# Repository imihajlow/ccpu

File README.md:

A 74xx discrete logic IC-based computer.

Folder structure:
* `doc` - documentation
* `model` - Verilog model and test benches
* `boards` - KiCAD designs of the computer
* `tools` - various tools: ALU generator, assembler, linker, compiler, simulator.
* `app` - software tests and applications

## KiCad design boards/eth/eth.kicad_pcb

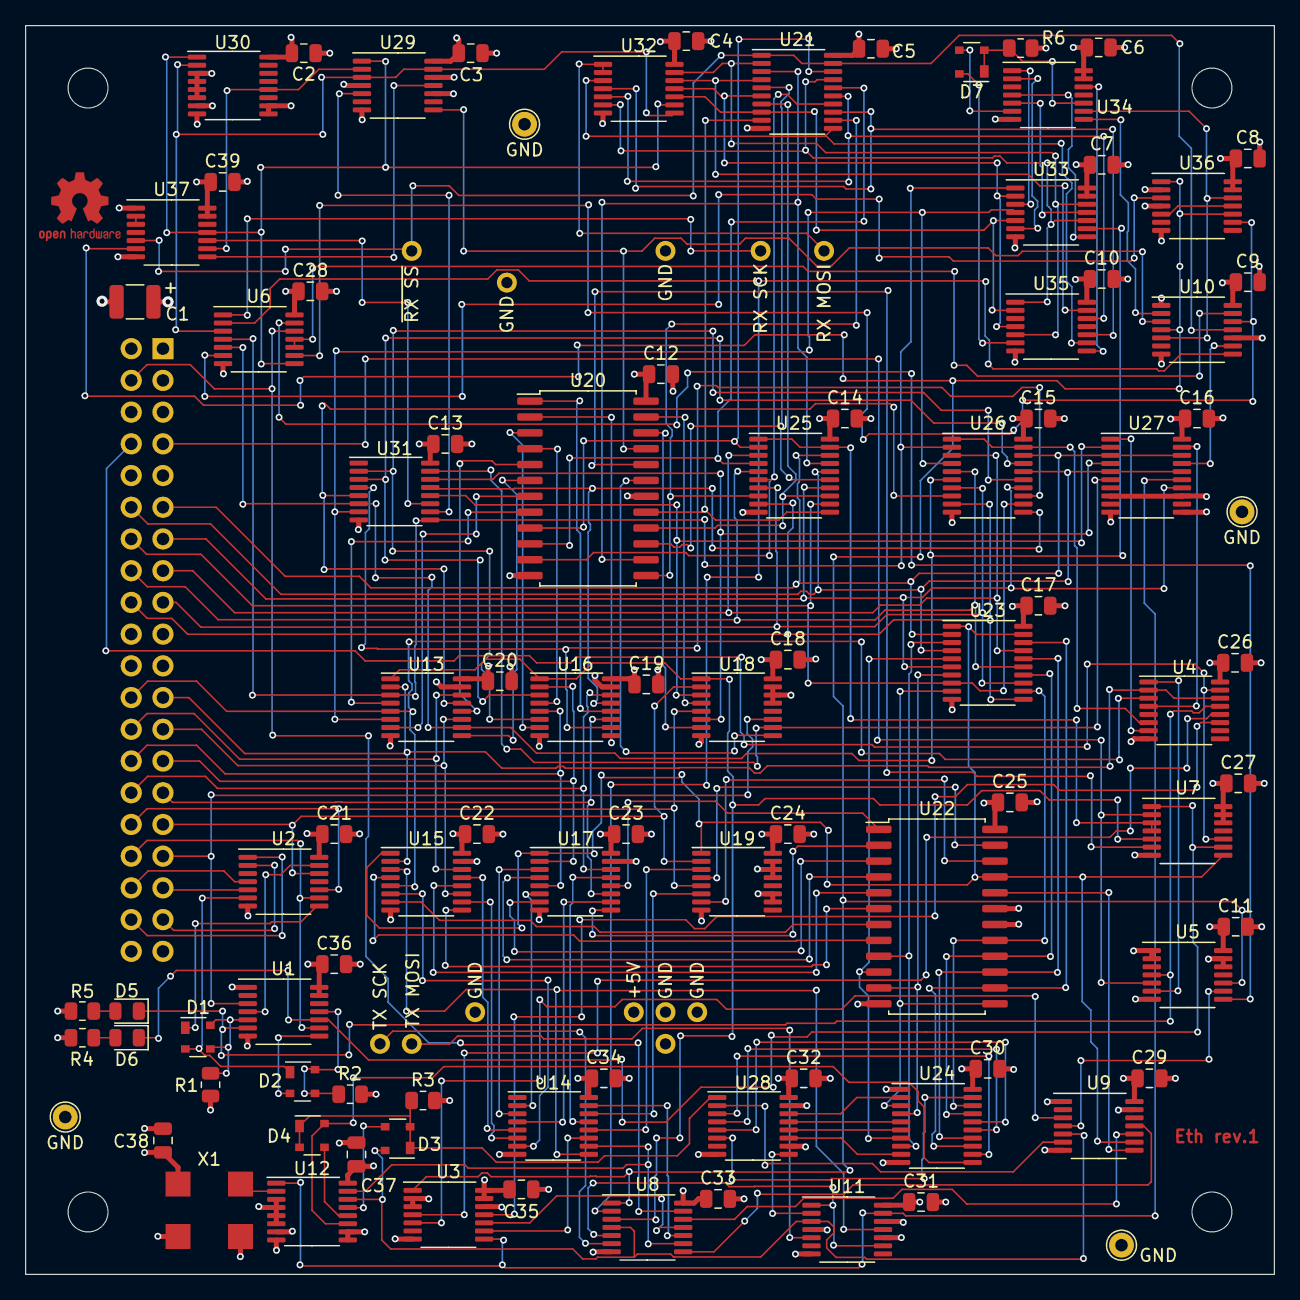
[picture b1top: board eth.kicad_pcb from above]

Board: 4 copper layers, 100.0 x 100.0 mm, 100 parts (1 on the bottom side), 173 nets.

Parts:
C1: 33.0x10v; C_1210_3225Metric
C2, C3, C4, C5, C6, C7, C8, C9, C10, C11, C12, C13, C14, C15, C16, C17, C18, C19, C20, C21, C22, C23, C24, C25, C26, C27, C28, C29, C30, C31, C32, C33, C34, C35, C36, C37, C38, C39: 0.1; C_0805_2012Metric
D1, D2, D3, D4, D7: BAT74; SOT-143
D5, D6: LED; LED_0805_2012Metric
H1, H2, H3, H4: MountingHole; MountingHole_3.2mm_M3
J1: Conn_02x20_Odd_Even; PinHeader_2x20_P2.54mm_Horizontal
J2: eth-phy-shield-conn; partial-nucleo64
R1, R2, R3, R6: 1k; R_0805_2012Metric
R4, R5: 500; R_0805_2012Metric
TP1, TP2, TP3, TP4: GND; TestPoint_THTPad_D2.0mm_Drill1.0mm
U1, U9, U37: 74HC04; TSSOP-14_4.4x5mm_P0.65mm
U2, U34, U35: 74HC21; TSSOP-14_4.4x5mm_P0.65mm
U3, U10, U11, U29, U36: 74HC74; TSSOP-14_4.4x5mm_P0.65mm
U4: 74HC139; TSSOP-16_4.4x5mm_P0.65mm
U5, U7: 74HC32; TSSOP-14_4.4x5mm_P0.65mm
U6, U8: 74HC08; TSSOP-14_4.4x5mm_P0.65mm
U12, U30: 74HC161; TSSOP-16_4.4x5mm_P0.65mm
U13, U15, U16, U17, U18, U19: 74HC157; TSSOP-16_4.4x5mm_P0.65mm
U14, U31: 74HC4040; TSSOP-16_4.4x5mm_P0.65mm
U20, U22: 6116; SOIC-24W_7.5x15.4mm_P1.27mm
U21, U23, U25, U26, U27: 74HC244; TSSOP-20_4.4x6.5mm_P0.65mm
U24: 74HC273; TSSOP-20_4.4x6.5mm_P0.65mm
U28: 74HC165; TSSOP-16_4.4x5mm_P0.65mm
U32: 74HC164; TSSOP-14_4.4x5mm_P0.65mm
U33: 74HC86; TSSOP-14_4.4x5mm_P0.65mm
X1: CB3-3C-20M; Oscillator_SMD_EuroQuartz_XO91-4Pin_7.0x5.0mm

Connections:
/a0: J1.23, U4.2 (A0), U4.14 (A0), U13.2 (I0a), U15.2 (I0a)
/a1: J1.24, U4.3 (A1), U13.5 (I0b), U15.5 (I0b)
/a2: J1.25, U13.11 (I0c), U15.11 (I0c)
/a3: J1.26, U13.14 (I0d), U15.14 (I0d)
/a4: J1.27, U16.2 (I0a), U17.2 (I0a)
/a5: J1.28, U16.5 (I0b), U17.5 (I0b)
/a6: J1.29, U16.11 (I0c), U17.11 (I0c)
/a7: J1.30, U16.14 (I0d), U17.14 (I0d)
/a8: J1.31, U2.12, U18.2 (I0a), U19.2 (I0a)
/a9: J1.32, U2.10, U18.5 (I0b), U19.5 (I0b)
/a10: J1.33, U1.3, U18.11 (I0c)
/a11: J1.34, U1.9, U2.9
/a12: J1.35, U2.5
/a13: J1.36, U2.4
/a14: J1.37, U2.2
/a15: J1.38, U2.1
/a_89nab_set: D1.1 (C1), U2.8
/a_cdef_set: D1.2 (C2), D2.1 (C1), U2.6
/buf_full: U10.9 (Q), U27.17 (2A0)
/d0: J1.11, U23.2 (1A0), U25.18 (1Y0), U26.18 (1Y0), U27.3 (2Y0), U27.18 (1Y0)
/d1: J1.12, U23.4 (1A1), U25.16 (1Y1), U26.16 (1Y1), U27.5 (2Y1), U27.16 (1Y1)
/d2: J1.13, U23.6 (1A2), U25.14 (1Y2), U26.14 (1Y2), U27.14 (1Y2)
/d3: J1.14, U23.8 (1A3), U25.12 (1Y3), U26.12 (1Y3)
/d4: J1.15, U23.17 (2A0), U25.3 (2Y0), U26.3 (2Y0)
/d5: J1.16, U23.15 (2A1), U25.5 (2Y1), U26.5 (2Y1)
/d6: J1.17, U23.13 (2A2), U25.7 (2Y2), U26.7 (2Y2)
/d7: J1.18, U23.11 (2A3), U25.9 (2Y3), U26.9 (2Y3)
/filter/a02: U6.6, U36.3 (C)
/filter/d_4320_mac: D7.3 (A2), U34.6
/filter/d_4320_ok: D7.1 (C1), D7.2 (C2), R6.2, U34.10
/filter/d_4320_set: D7.4 (A1), U35.6
/filter/d_7651_set: U34.12, U35.8
/filter/d_xor_a0: U33.3, U34.1
/filter/d_xor_a1: U33.6, U34.2
/filter/d_xor_a2: U33.8, U34.4
/filter/last_mac_ok: U10.5 (Q), U34.9, U36.12 (D)
/filter/mac_end: U36.5 (Q), U36.11 (C)
/filter/next_mac_ok: U10.2 (D), U34.8
/filter/~d0: U33.11, U34.5
/rearm_sched: U3.5 (Q), U9.3
/receiver/bit_count2: U29.2 (D), U30.12 (Q2), U37.9
/receiver/byte_clk: U29.5 (Q), U31.10 (CP)
/receiver/rst: U31.11 (MR), U37.10
/receiver/sck_f: U6.3, U29.3 (C), U29.13 (~R), U30.2 (CP), U32.8 (CP)
/receiver/~bit_count_2: U29.11 (C), U37.8
/recv_a0: U13.4 (Za), U20.8 (A0)
/recv_a1: U13.7 (Zb), U20.7 (A1)
/recv_a2: U13.9 (Zc), U20.6 (A2)
/recv_a3: U13.12 (Zd), U20.5 (A3)
/recv_a4: U16.4 (Za), U20.4 (A4)
/recv_a5: U16.7 (Zb), U20.3 (A5)
/recv_a6: U16.9 (Zc), U20.2 (A6)
/recv_a7: U16.12 (Zd), U20.1 (A7)
/recv_a8: U18.4 (Za), U20.23 (A8)
/recv_a9: U18.7 (Zb), U20.22 (A9)
/recv_a10: U18.9 (Zc), U20.19 (A10)
/recv_a_sel: U7.5, U8.3, U13.1 (S), U16.1 (S), U18.1 (S)
/recv_byte0: U21.2 (1A0), U32.13 (Q7), U33.12, U35.5
/recv_byte1: U21.4 (1A1), U32.12 (Q6), U35.13
/recv_byte2: U21.6 (1A2), U32.11 (Q5), U33.2, U35.4
/recv_byte3: U21.8 (1A3), U32.10 (Q4), U33.5, U35.2
/recv_byte4: U21.17 (2A0), U32.6 (Q3), U33.10, U35.1
/recv_byte5: U21.15 (2A1), U32.5 (Q2), U35.12
/recv_byte6: U21.13 (2A2), U32.4 (Q1), U35.10
/recv_byte7: U21.11 (2A3), U32.3 (Q0), U35.9
/recv_byte_cnt0: U6.4, U13.3 (I1a), U26.2 (1A0), U31.9 (Q0), U33.1
/recv_byte_cnt1: U13.6 (I1b), U26.4 (1A1), U31.7 (Q1), U33.4
/recv_byte_cnt2: U6.5, U13.10 (I1c), U26.6 (1A2), U31.6 (Q2), U33.9
/recv_byte_cnt3: U13.13 (I1d), U26.8 (1A3), U31.5 (Q3)
/recv_byte_cnt4: U16.3 (I1a), U26.17 (2A0), U31.3 (Q4)
/recv_byte_cnt5: U16.6 (I1b), U26.15 (2A1), U31.2 (Q5)
/recv_byte_cnt6: U16.10 (I1c), U26.13 (2A2), U31.4 (Q6)
/recv_byte_cnt7: U16.13 (I1d), U26.11 (2A3), U31.13 (Q7)
/recv_byte_cnt8: U18.3 (I1a), U27.2 (1A0), U31.12 (Q8)
/recv_byte_cnt9: U18.6 (I1b), U27.4 (1A1), U31.14 (Q9)
/recv_byte_cnt10: U18.10 (I1c), U27.6 (1A2), U31.15 (Q10)
/recv_d0: U20.9 (D0), U21.18 (1Y0), U25.2 (1A0)
/recv_d1: U20.10 (D1), U21.16 (1Y1), U25.4 (1A1)
/recv_d2: U20.11 (D2), U21.14 (1Y2), U25.6 (1A2)
/recv_d3: U20.13 (D3), U21.12 (1Y3), U25.8 (1A3)
/recv_d4: U20.14 (D4), U21.3 (2Y0), U25.17 (2A0)
/recv_d5: U20.15 (D5), U21.5 (2Y1), U25.15 (2A1)
/recv_d6: U20.16 (D6), U21.7 (2Y2), U25.13 (2A2)
/recv_d7: U20.17 (D7), U21.9 (2Y3), U25.11 (2A3)
/recv_mosi: J2.PB13, U32.1 (DSA), U32.2 (DSB)
/recv_sck: J2.PB15, U6.1
/recv_sck_ena: U6.2, U8.2, U10.8 (~Q)
/recv_ss: U3.1 (~R), U5.10, U8.1, U10.4 (~S), U36.1 (~R), U36.10 (~S), U37.6
/tx_a0: U15.4 (Za), U22.8 (A0)
/tx_a1: U15.7 (Zb), U22.7 (A1)
/tx_a2: U15.9 (Zc), U22.6 (A2)
/tx_a3: U15.12 (Zd), U22.5 (A3)
/tx_a4: U17.4 (Za), U22.4 (A4)
/tx_a5: U17.7 (Zb), U22.3 (A5)
/tx_a6: U17.9 (Zc), U22.2 (A6)
/tx_a7: U17.12 (Zd), U22.1 (A7)
/tx_a8: U19.4 (Za), U22.23 (A8)
/tx_a9: U19.7 (Zb), U22.22 (A9)
/tx_buf_d0: U24.9 (Q3), U28.11 (D0)
/tx_buf_d1: U24.6 (Q2), U28.12 (D1)
/tx_buf_d2: U24.5 (Q1), U28.13 (D2)
/tx_buf_d3: U24.2 (Q0), U28.14 (D3)
/tx_buf_d4: U24.12 (Q4), U28.3 (D4)
/tx_buf_d5: U24.15 (Q5), U28.4 (D5)
/tx_buf_d6: U24.16 (Q6), U28.5 (D6)
/tx_buf_d7: U24.19 (Q7), U28.6 (D7)
/tx_byte_cnt0: U11.11 (C), U14.9 (Q0), U15.3 (I1a)
/tx_byte_cnt1: U14.7 (Q1), U15.6 (I1b)
/tx_byte_cnt2: U14.6 (Q2), U15.10 (I1c)
/tx_byte_cnt3: U14.5 (Q3), U15.13 (I1d)
/tx_byte_cnt4: U14.3 (Q4), U17.3 (I1a)
/tx_byte_cnt5: U14.2 (Q5), U17.6 (I1b)
/tx_byte_cnt6: U14.4 (Q6), U17.10 (I1c)
/tx_byte_cnt7: U14.13 (Q7), U17.13 (I1d)
/tx_byte_cnt8: U14.12 (Q8), U19.3 (I1a)
/tx_byte_cnt9: U14.14 (Q9), U19.6 (I1b)
/tx_byte_cnt10: U8.10, U14.15 (Q10)
/tx_cnt0: D3.4 (A1), U8.4, U9.5, U11.3 (C), U12.14 (Q0)
/tx_cnt1: D3.3 (A2), U12.13 (Q1)
/tx_cnt2: D4.3 (A2), U12.12 (Q2)
/tx_cnt3: D4.4 (A1), U12.11 (Q3), U24.11 (Cp)
/tx_cp_in: U12.2 (CP), X1.3 (OUT)
/tx_d0: U22.14 (D4), U23.18 (1Y0), U24.13 (D4)
/tx_d1: U22.15 (D5), U23.16 (1Y1), U24.14 (D5)
/tx_d2: U22.16 (D6), U23.14 (1Y2), U24.17 (D6)
/tx_d3: U22.17 (D7), U23.12 (1Y3), U24.18 (D7)
/tx_d4: U22.9 (D0), U23.3 (2Y0), U24.8 (D3)
/tx_d5: U22.10 (D1), U23.5 (2Y1), U24.7 (D2)
/tx_d6: U22.11 (D2), U23.7 (2Y2), U24.4 (D1)
/tx_d7: U22.13 (D3), U23.9 (2Y3), U24.3 (D0)
/tx_finish: U8.8, U9.11
/tx_halt: U3.9 (Q), U14.11 (MR)
/tx_mosi: J2.PC12, U11.5 (Q)
/tx_oe: U8.5, U11.1 (~R), U11.9 (Q)
/tx_sck: J2.PC10, U8.6
/tx_shift_cp: U9.6, U28.2 (CP)
/tx_shift_q7: U11.2 (D), U28.9 (Q7)
/~a10: U1.4, U2.13
/~a11: D2.2 (C2), U1.8
/~a_buf_sel: D6.1 (K), U1.10, U7.1, U7.9
/~a_fbxx: D5.1 (K), U1.6, U4.13 (A1), U5.4
/~clr_frame_received: U6.10, U6.11, U10.13 (~R)
/~inhibit: U6.9, U10.12 (D), U36.9 (Q)
/~oe_cr_to_d: U4.4 (O0), U27.19 (2OE)
/~oe: J1.7, U5.5, U7.2
/~rearm_req: U3.4 (~S), U4.12 (O0)
/~rearm_sched: U5.9, U9.4
/~rearm: U5.8, U6.13
/~recv_buf_oe: U7.6, U20.20 (~OE)
/~recv_buf_we: U10.3 (C), U20.21 (~WE), U29.8 (~Q)
/~recv_byte_cnt_hi_oe: U4.7 (O3), U27.1 (1OE)
/~recv_byte_cnt_lo_oe: U4.6 (O2), U26.1 (1OE), U26.19 (2OE)
/~recv_d_oe: U7.3, U7.4, U25.1 (1OE), U25.19 (2OE)
/~recv_rst: U6.8, U29.1 (~R), U30.1 (~MR), U32.9 (~MR), U37.11
/~recv_ss: J2.PC6, U10.11 (C), U21.1 (1OE), U21.19 (2OE), U37.5
/~reg_oe_ena: U4.1 (E), U5.6
/~rst: J1.4, U6.12, U8.13
/~tx_buf_oe: U9.8, U22.20 (~OE)
/~tx_buf_we: U7.8, U9.9, U15.1 (S), U17.1 (S), U19.1 (S), U22.21 (~WE), U23.1 (1OE), U23.19 (2OE)
/~tx_byte_clk: U8.9, U12.15 (TC), U14.10 (CP)
/~tx_finish: U8.12, U9.10
/~tx_halt_set: U3.10 (~S), U8.11
/~tx_halt: U3.8 (~Q), U11.13 (~R), U12.1 (~MR), U27.15 (2A1)
/~tx_req: U3.11 (C), U4.11 (O1)
/~tx_shift_pl: D3.1 (C1), D3.2 (C2), D4.1 (C1), D4.2 (C2), R3.1, U28.1 (~PL)
/~we: J1.8, U4.15 (E), U7.10
GND: C1.2, C2.2, C3.2, C4.2, C5.2, C6.2, C7.2, C8.2, C9.2, C10.2, C11.2, C12.2, C13.2, C14.2, C15.2, C16.2, C17.2, C18.2, C19.2, C20.2, C21.2, C22.2, C23.2, C24.2, C25.2, C26.2, C27.2, C28.2, C29.2, C30.2, C31.2, C32.2, C33.2, C34.2, C35.2, C36.2, C37.2, C38.2, C39.2, J1.2, J1.39, J2.GND, R3.2, R6.1, TP1.1, TP2.1, TP3.1, TP4.1, U1.1, U1.7 (GND), U2.7 (GND), U3.2 (D), U3.3 (C), U3.7 (GND), U3.12 (D), U4.8 (GND), U5.1, U5.2, U5.7 (GND), U5.12, U5.13, U6.7 (GND), U7.7 (GND), U8.7 (GND), U9.1, U9.7 (GND), U9.13, U10.7 (GND), U11.7 (GND), U12.3 (D0), U12.4 (D1), U12.5 (D2), U12.6 (D3), U12.8 (GND), U13.8 (GND), U13.15 (E), U14.8 (GND), U15.8 (GND), U15.15 (E), U16.8 (GND), U16.15 (E), U17.8 (GND), U17.15 (E), U18.8 (GND), U18.13 (I1d), U18.14 (I0d), U18.15 (E), U19.8 (GND), U19.10 (I1c), U19.11 (I0c), U19.13 (I1d), U19.14 (I0d), U19.15 (E), U20.12 (GND), U20.18 (~CS), U21.10 (GND), U22.12 (GND), U22.18 (~CS), U22.19 (A10), U23.10 (GND), U24.10 (GND), U25.10 (GND), U26.10 (GND), U27.8 (1A3), U27.10 (GND), U27.11 (2A3), U27.13 (2A2), U28.8 (GND), U28.10 (DS), U28.15 (~CE), U29.7 (GND), U30.3 (D0), U30.4 (D1), U30.5 (D2), U30.6 (D3), U30.8 (GND), U31.8 (GND), U32.7 (GND), U33.7 (GND), U34.7 (GND), U35.7 (GND), U36.7 (GND), U37.1, U37.7 (GND), X1.2 (GND)
unnamed: D1.3 (A2), D1.4 (A1), R1.2, U1.5
unnamed: D2.3 (A2), D2.4 (A1), R2.1, U1.11
unnamed: D5.2 (A), R5.1
unnamed: D6.2 (A), R4.2
unnamed: U37.2, U37.3
VCC: C1.1, C2.1, C3.1, C4.1, C5.1, C6.1, C7.1, C8.1, C9.1, C10.1, C11.1, C12.1, C13.1, C14.1, C15.1, C16.1, C17.1, C18.1, C19.1, C20.1, C21.1, C22.1, C23.1, C24.1, C25.1, C26.1, C27.1, C28.1, C29.1, C30.1, C31.1, C32.1, C33.1, C34.1, C35.1, C36.1, C37.1, C38.1, C39.1, J1.1, J1.40, J2.+5V, R1.1, R2.2, R4.1, R5.2, U1.13, U1.14 (VCC), U2.14 (VCC), U3.13 (~R), U3.14 (VCC), U4.16 (VCC), U5.14 (VCC), U6.14 (VCC), U7.12, U7.13, U7.14 (VCC), U8.14 (VCC), U9.14 (VCC), U10.1 (~R), U10.10 (~S), U10.14 (VCC), U11.4 (~S), U11.10 (~S), U11.12 (D), U11.14 (VCC), U12.7 (CEP), U12.9 (~PE), U12.10 (CET), U12.16 (VCC), U13.16 (VCC), U14.16 (VCC), U15.16 (VCC), U16.16 (VCC), U17.16 (VCC), U18.16 (VCC), U19.16 (VCC), U20.24 (VCC), U21.20 (VCC), U22.24 (VCC), U23.20 (VCC), U24.1 (~Mr), U24.20 (VCC), U25.20 (VCC), U26.20 (VCC), U27.20 (VCC), U28.16 (VCC), U29.4 (~S), U29.10 (~S), U29.12 (D), U29.14 (VCC), U30.7 (CEP), U30.9 (~PE), U30.10 (CET), U30.16 (VCC), U31.16 (VCC), U32.14 (VCC), U33.13, U33.14 (VCC), U34.13, U34.14 (VCC), U35.14 (VCC), U36.2 (D), U36.4 (~S), U36.13 (~R), U36.14 (VCC), U37.13, U37.14 (VCC), X1.1 (EN), X1.4 (V+)

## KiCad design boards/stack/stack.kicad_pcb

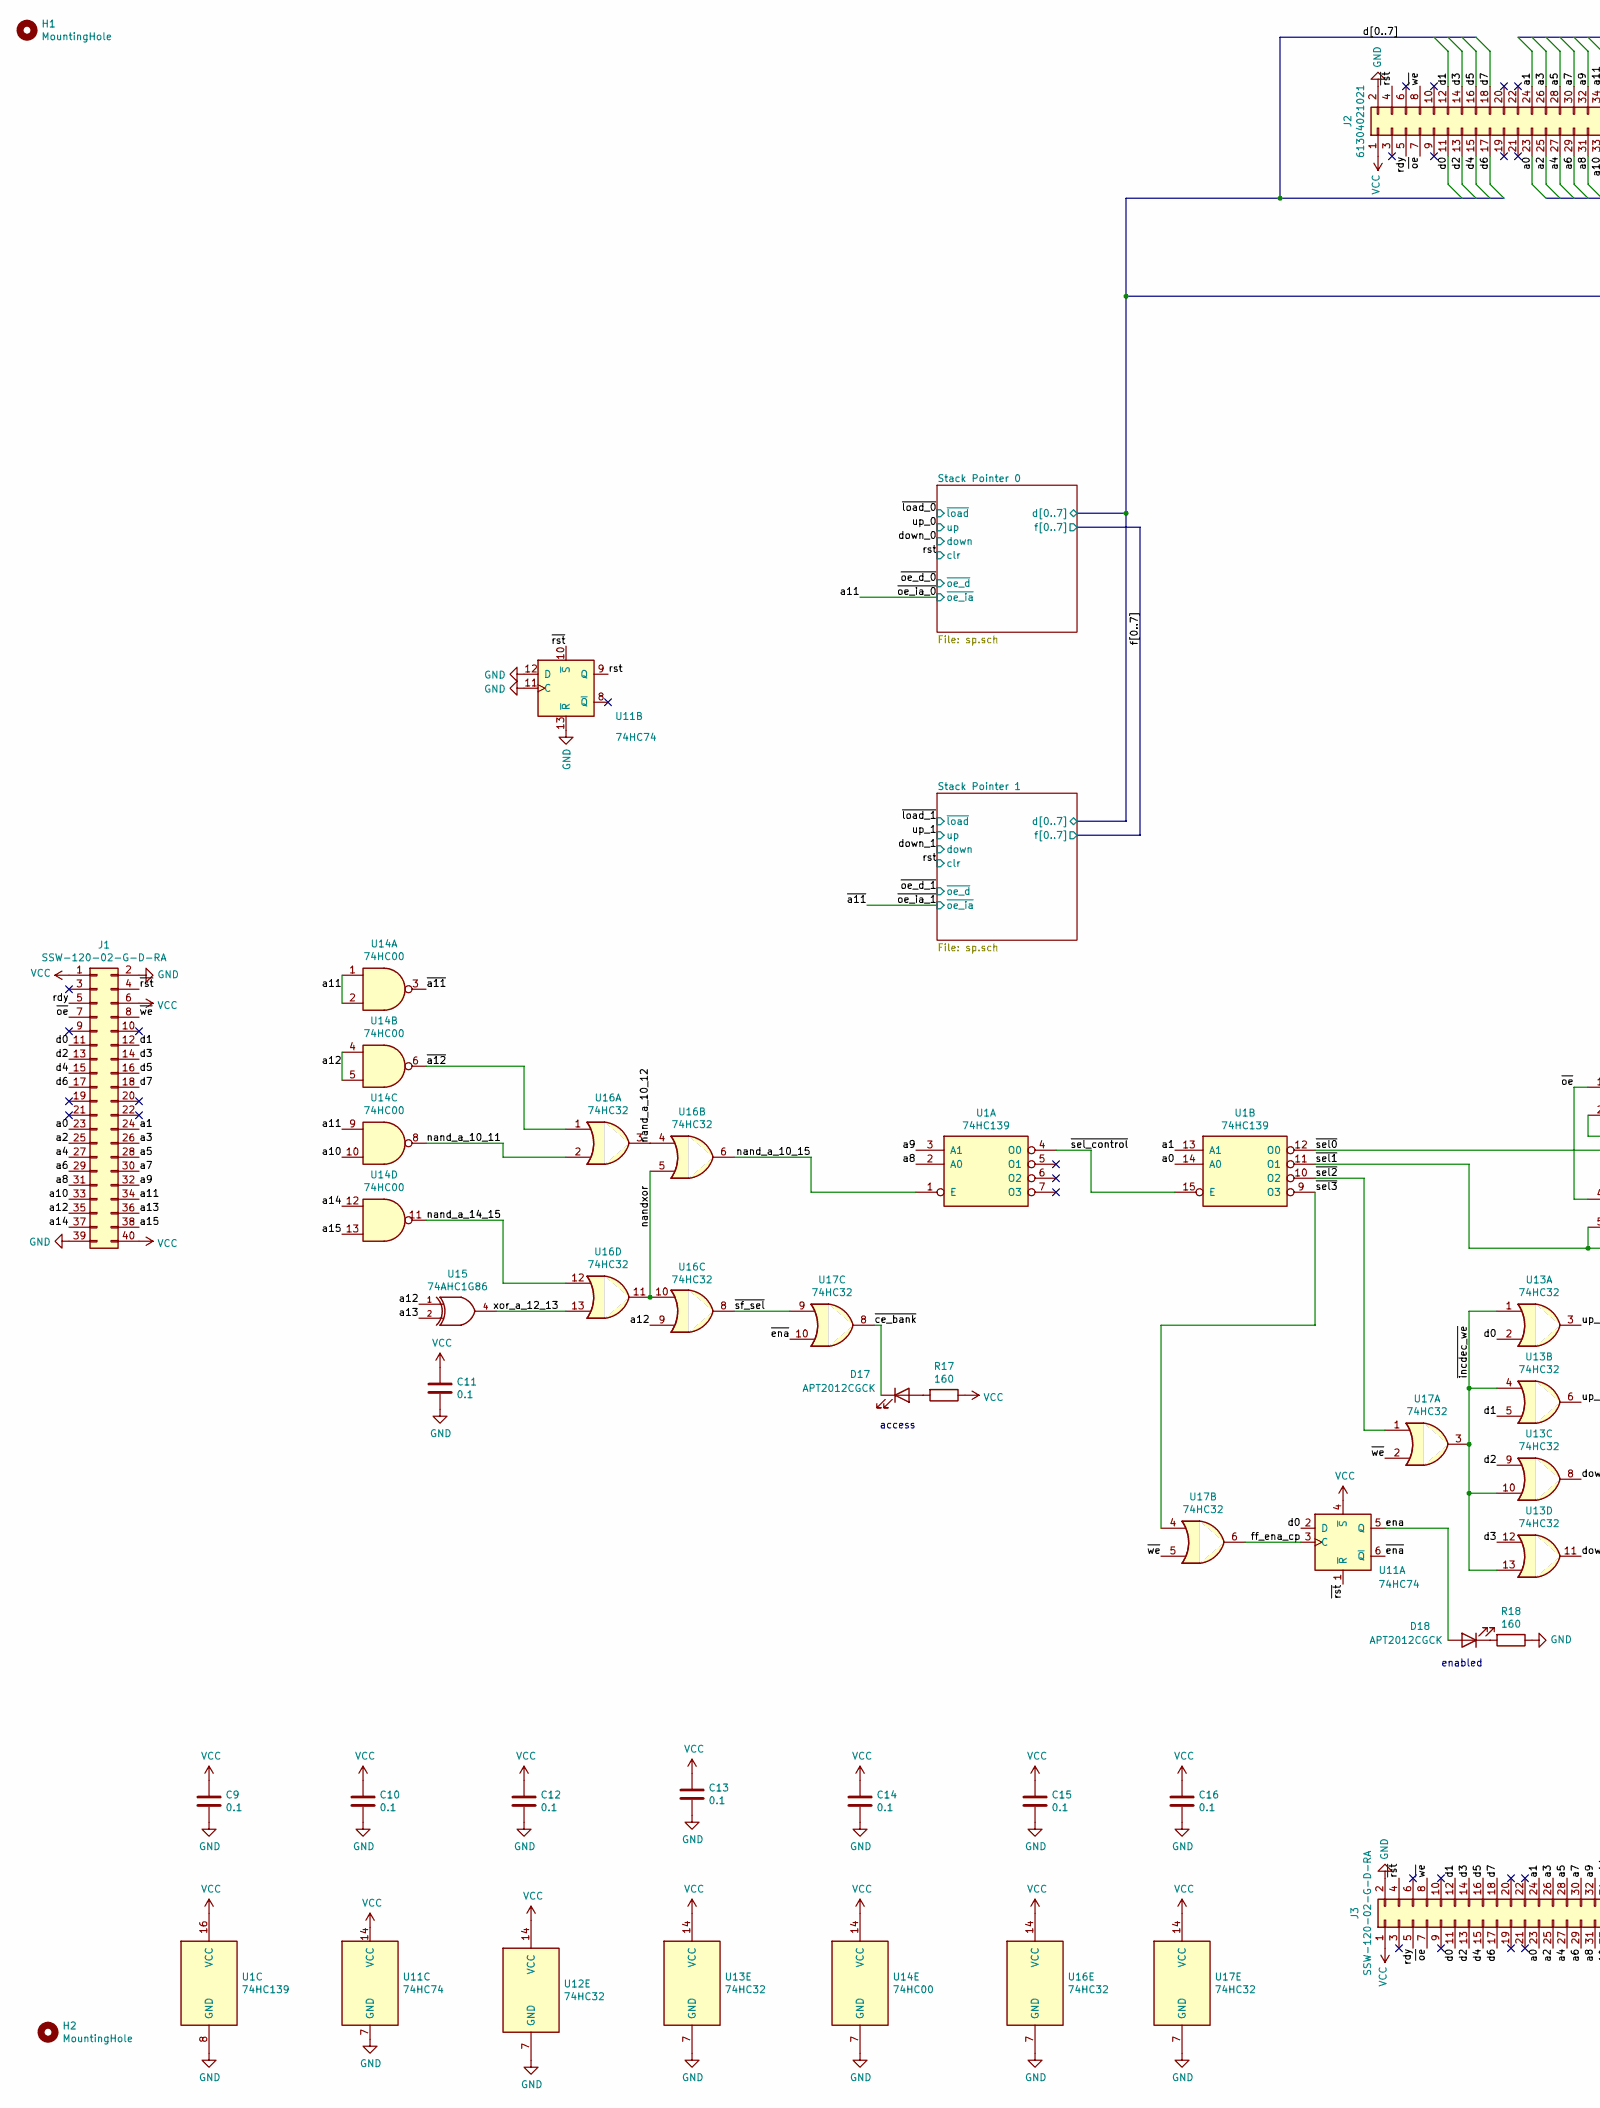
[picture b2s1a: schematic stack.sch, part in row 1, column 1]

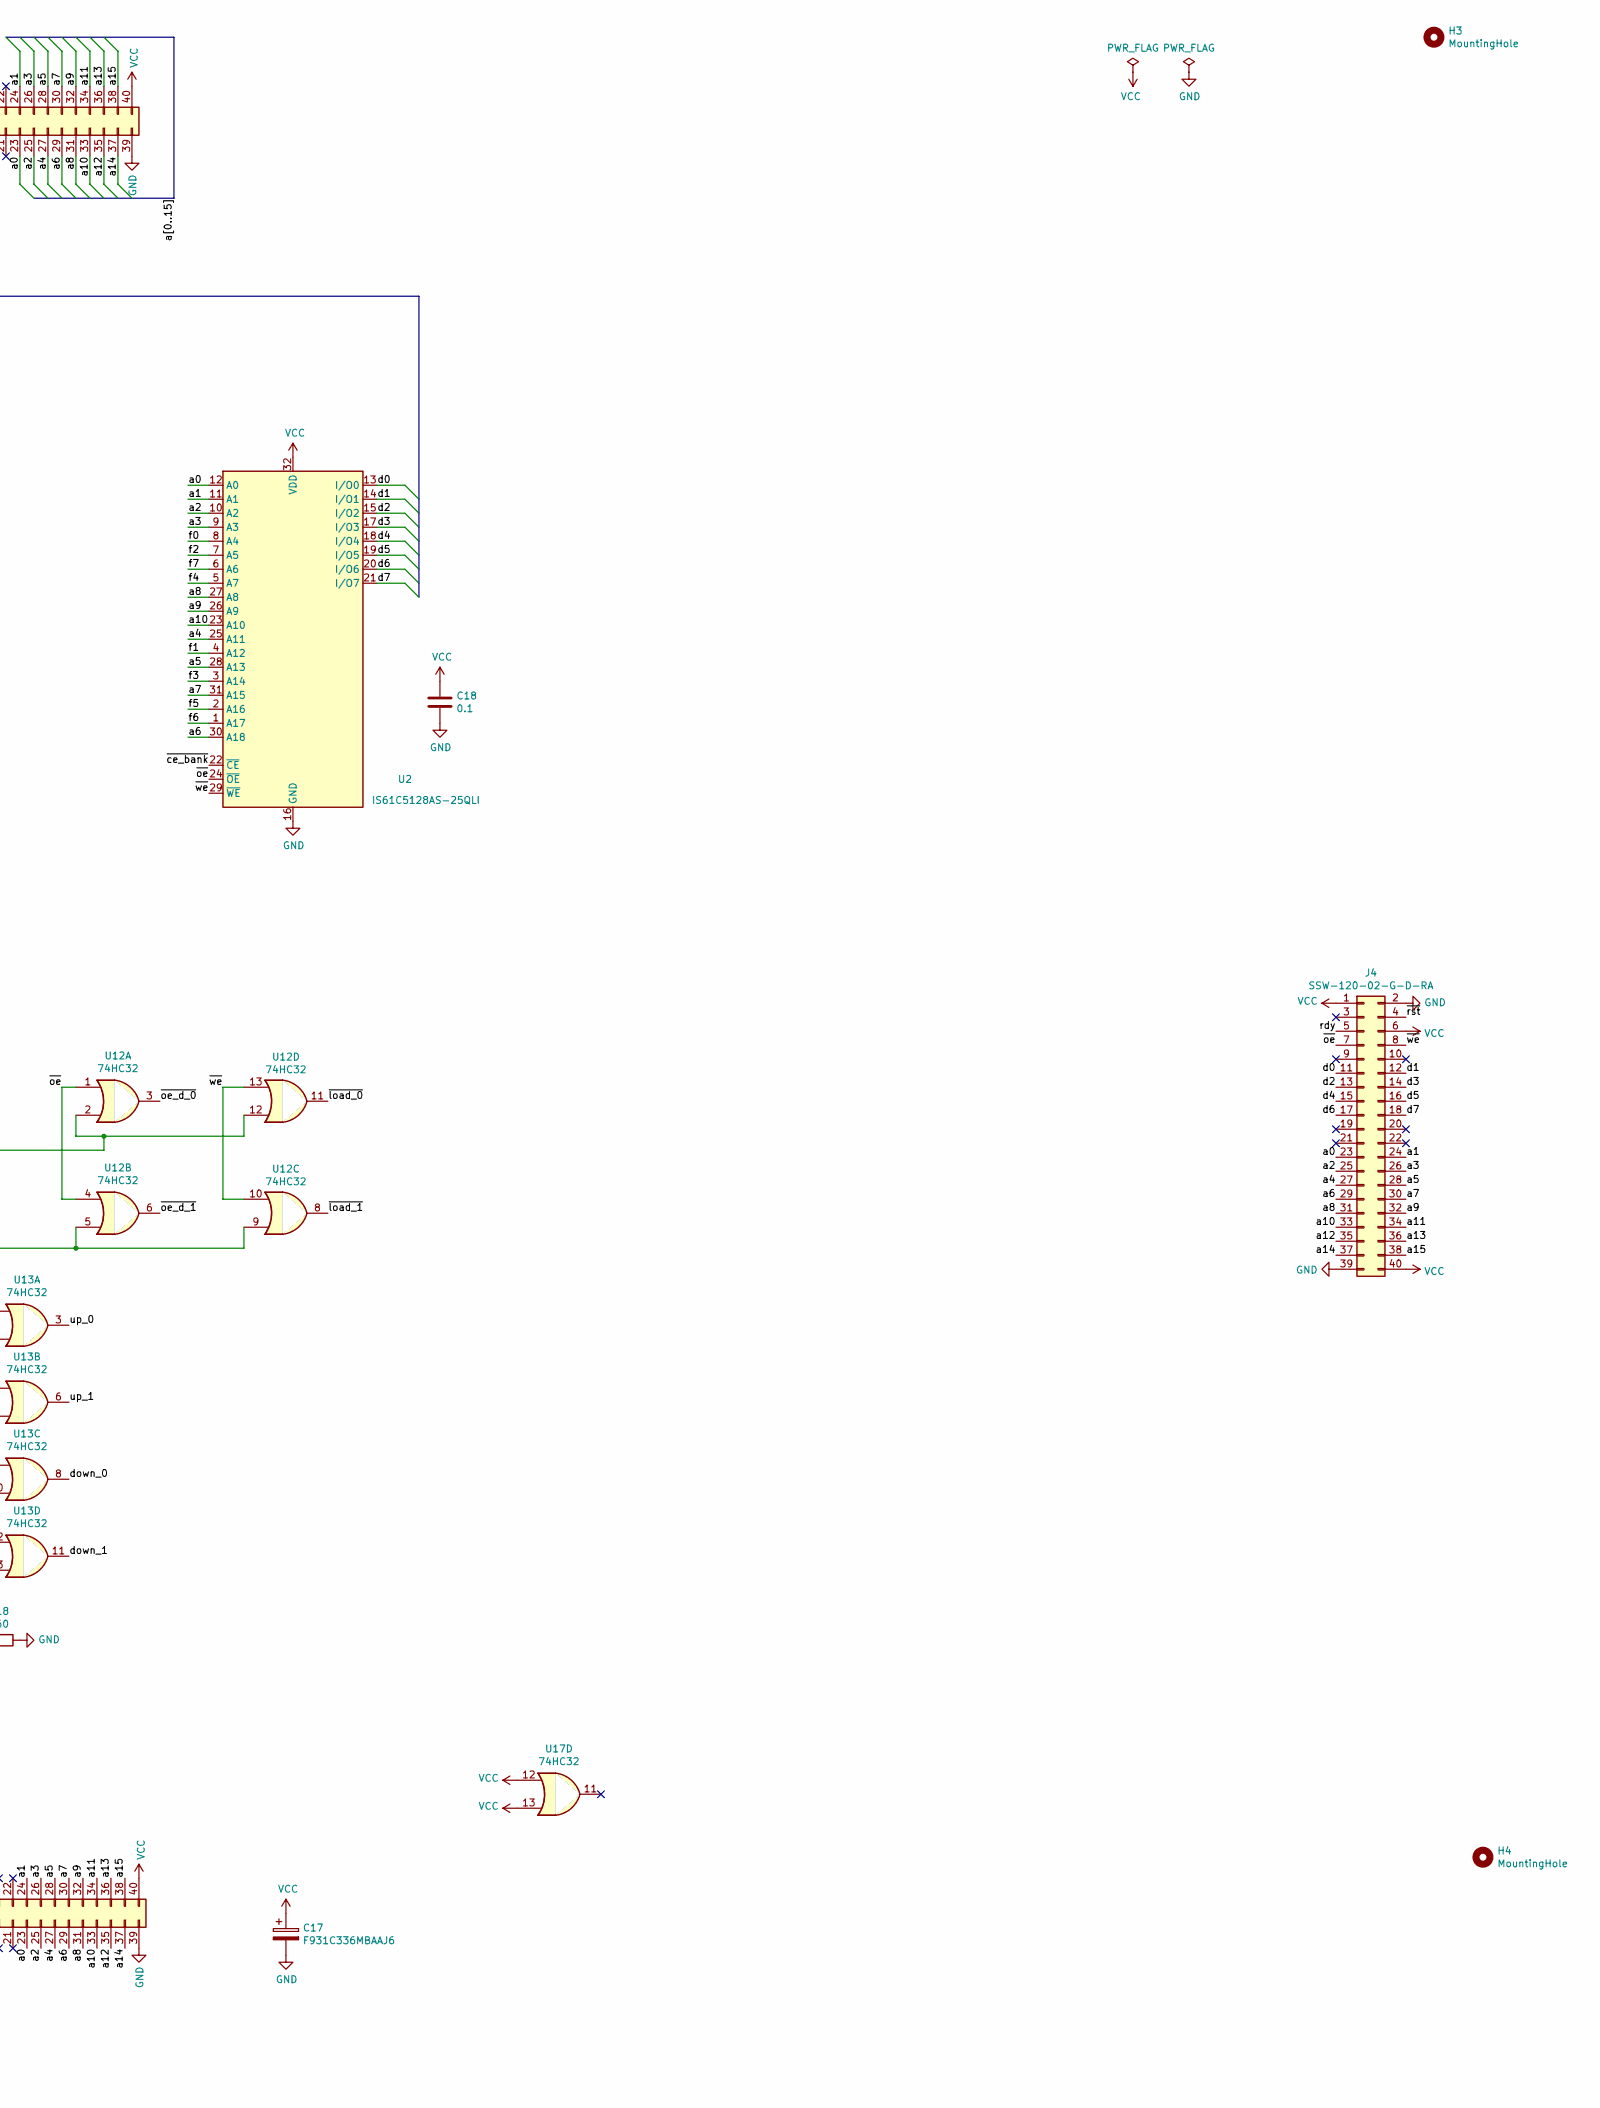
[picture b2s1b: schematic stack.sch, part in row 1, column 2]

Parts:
C9, C10, C11, C12, C13, C14, C15, C16, C18: 0.1; C_0805_2012Metric
C17: F931C336MBAAJ6‎; CP_EIA-3528-21_Kemet-B_Pad1.50x2.35mm_HandSolder
D17, D18: APT2012CGCK; LED_0805_2012Metric
H1, H2, H3, H4: MountingHole; MountingHole_3.2mm_M3
J1, J3, J4: SSW-120-02-G-D-RA; PinSocket_2x20_P2.54mm_Horizontal
J2: 61304021021; PinHeader_2x20_P2.54mm_Horizontal
R17, R18: 160; R_0805_2012Metric
U1: 74HC139; TSSOP-16_4.4x5mm_P0.65mm
U2: IS61C5128AS-25QLI; SSOP-32_11.305x20.495mm_P1.27mm
U11: 74HC74; TSSOP-14_4.4x5mm_P0.65mm
U12, U13, U16, U17: 74HC32; TSSOP-14_4.4x5mm_P0.65mm
U14: 74HC00; TSSOP-14_4.4x5mm_P0.65mm
U15: 74AHC1G86; SOT-23-5

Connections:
/a0: J1.23, J2.23, J3.23, J4.23, U1.14 (A0), U2.12 (A0)
/a1: J1.24, J2.24, J3.24, J4.24, U1.13 (A1), U2.11 (A1)
/a2: J1.25, J2.25, J3.25, J4.25, U2.10 (A2)
/a3: J1.26, J2.26, J3.26, J4.26, U2.9 (A3)
/a4: J1.27, J2.27, J3.27, J4.27, U2.25 (A11)
/a5: J1.28, J2.28, J3.28, J4.28, U2.28 (A13)
/a6: J1.29, J2.29, J3.29, J4.29, U2.30 (A18)
/a7: J1.30, J2.30, J3.30, J4.30, U2.31 (A15)
/a8: J1.31, J2.31, J3.31, J4.31, U1.2 (A0), U2.27 (A8)
/a9: J1.32, J2.32, J3.32, J4.32, U1.3 (A1), U2.26 (A9)
/a10: J1.33, J2.33, J3.33, J4.33, U2.23 (A10), U14.10
/a11: J1.34, J2.34, J3.34, J4.34, U14.1, U14.2, U14.9; also elsewhere on the board
/a12: J1.35, J2.35, J3.35, J4.35, U14.4, U14.5, U15.1, U16.9
/a13: J1.36, J2.36, J3.36, J4.36, U15.2
/a14: J1.37, J2.37, J3.37, J4.37, U14.12
/a15: J1.38, J2.38, J3.38, J4.38, U14.13
/d0: J1.11, J2.11, J3.11, J4.11, U2.13 (I/O0), U11.2 (D), U13.2; also elsewhere on the board
/d1: J1.12, J2.12, J3.12, J4.12, U2.14 (I/O1), U13.5; also elsewhere on the board
/d2: J1.13, J2.13, J3.13, J4.13, U2.15 (I/O2), U13.9; also elsewhere on the board
/d3: J1.14, J2.14, J3.14, J4.14, U2.17 (I/O3), U13.12; also elsewhere on the board
/d4: J1.15, J2.15, J3.15, J4.15, U2.18 (I/O4); also elsewhere on the board
/d5: J1.16, J2.16, J3.16, J4.16, U2.19 (I/O5); also elsewhere on the board
/d6: J1.17, J2.17, J3.17, J4.17, U2.20 (I/O6); also elsewhere on the board
/d7: J1.18, J2.18, J3.18, J4.18, U2.21 (I/O7); also elsewhere on the board
/down_0: U13.8; also elsewhere on the board
/down_1: U13.11; also elsewhere on the board
/ena: D18.2 (A), U11.5 (Q)
/f0: U2.8 (A4); also elsewhere on the board
/f1: U2.4 (A12); also elsewhere on the board
/f2: U2.7 (A5); also elsewhere on the board
/f3: U2.3 (A14); also elsewhere on the board
/f4: U2.5 (A7); also elsewhere on the board
/f5: U2.2 (A16); also elsewhere on the board
/f6: U2.1 (A17); also elsewhere on the board
/f7: U2.6 (A6); also elsewhere on the board
/ff_ena_cp: U11.3 (C), U17.6
/nand_a_10_11: U14.8, U16.2
/nand_a_10_12: U16.3, U16.4
/nand_a_10_15: U1.1 (E), U16.6
/nand_a_14_15: U14.11, U16.12
/nandxor: U16.5, U16.10, U16.11
/rdy: J1.5, J2.5, J3.5, J4.5
/rst: U11.9 (Q); also elsewhere on the board
/up_0: U13.3; also elsewhere on the board
/up_1: U13.6; also elsewhere on the board
/xor_a_12_13: U15.4, U16.13
/~a11: U14.3; also elsewhere on the board
/~a12: U14.6, U16.1
/~ce_bank: D17.1 (K), U2.22 (~CE), U17.8
/~ena: U11.6 (~Q), U17.10
/~incdec_we: U13.1, U13.4, U13.10, U13.13, U17.3
/~load_0: U12.11; also elsewhere on the board
/~load_1: U12.8; also elsewhere on the board
/~oe: J1.7, J2.7, J3.7, J4.7, U2.24 (~OE), U12.1, U12.4
/~oe_d_0: U12.3; also elsewhere on the board
/~oe_d_1: U12.6; also elsewhere on the board
/~rst: J1.4, J2.4, J3.4, J4.4, U11.1 (~R), U11.10 (~S)
/~sel0: U1.12 (O0), U12.2, U12.12
/~sel1: U1.11 (O1), U12.5, U12.9
/~sel2: U1.10 (O2), U17.1
/~sel3: U1.9 (O3), U17.4
/~sel_control: U1.4 (O0), U1.15 (E)
/~sf_sel: U16.8, U17.9
/~we: J1.8, J2.8, J3.8, J4.8, U2.29 (~WE), U12.10, U12.13, U17.2, U17.5
GND: C9.2, C10.2, C11.2, C12.2, C13.2, C14.2, C15.2, C16.2, C17.2, C18.2, J1.2, J1.39, J2.2, J2.39, J3.2, J3.39, J4.2, J4.39, R18.1, U1.8 (GND), U2.16 (GND), U11.7 (GND), U11.11 (C), U11.12 (D), U11.13 (~R), U12.7 (GND), U13.7 (GND), U14.7 (GND), U15.3 (GND), U16.7 (GND), U17.7 (GND); also elsewhere on the board
unnamed: D17.2 (A), R17.2
unnamed: D18.1 (K), R18.2
VCC: C9.1, C10.1, C11.1, C12.1, C13.1, C14.1, C15.1, C16.1, C17.1, C18.1, J1.1, J1.6, J1.40, J2.1, J2.40, J3.1, J3.40, J4.1, J4.6, J4.40, R17.1, U1.16 (VCC), U2.32 (VDD), U11.4 (~S), U11.14 (VCC), U12.14 (VCC), U13.14 (VCC), U14.14 (VCC), U15.5 (VCC), U16.14 (VCC), U17.12, U17.13, U17.14 (VCC); also elsewhere on the board

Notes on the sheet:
access
enabled

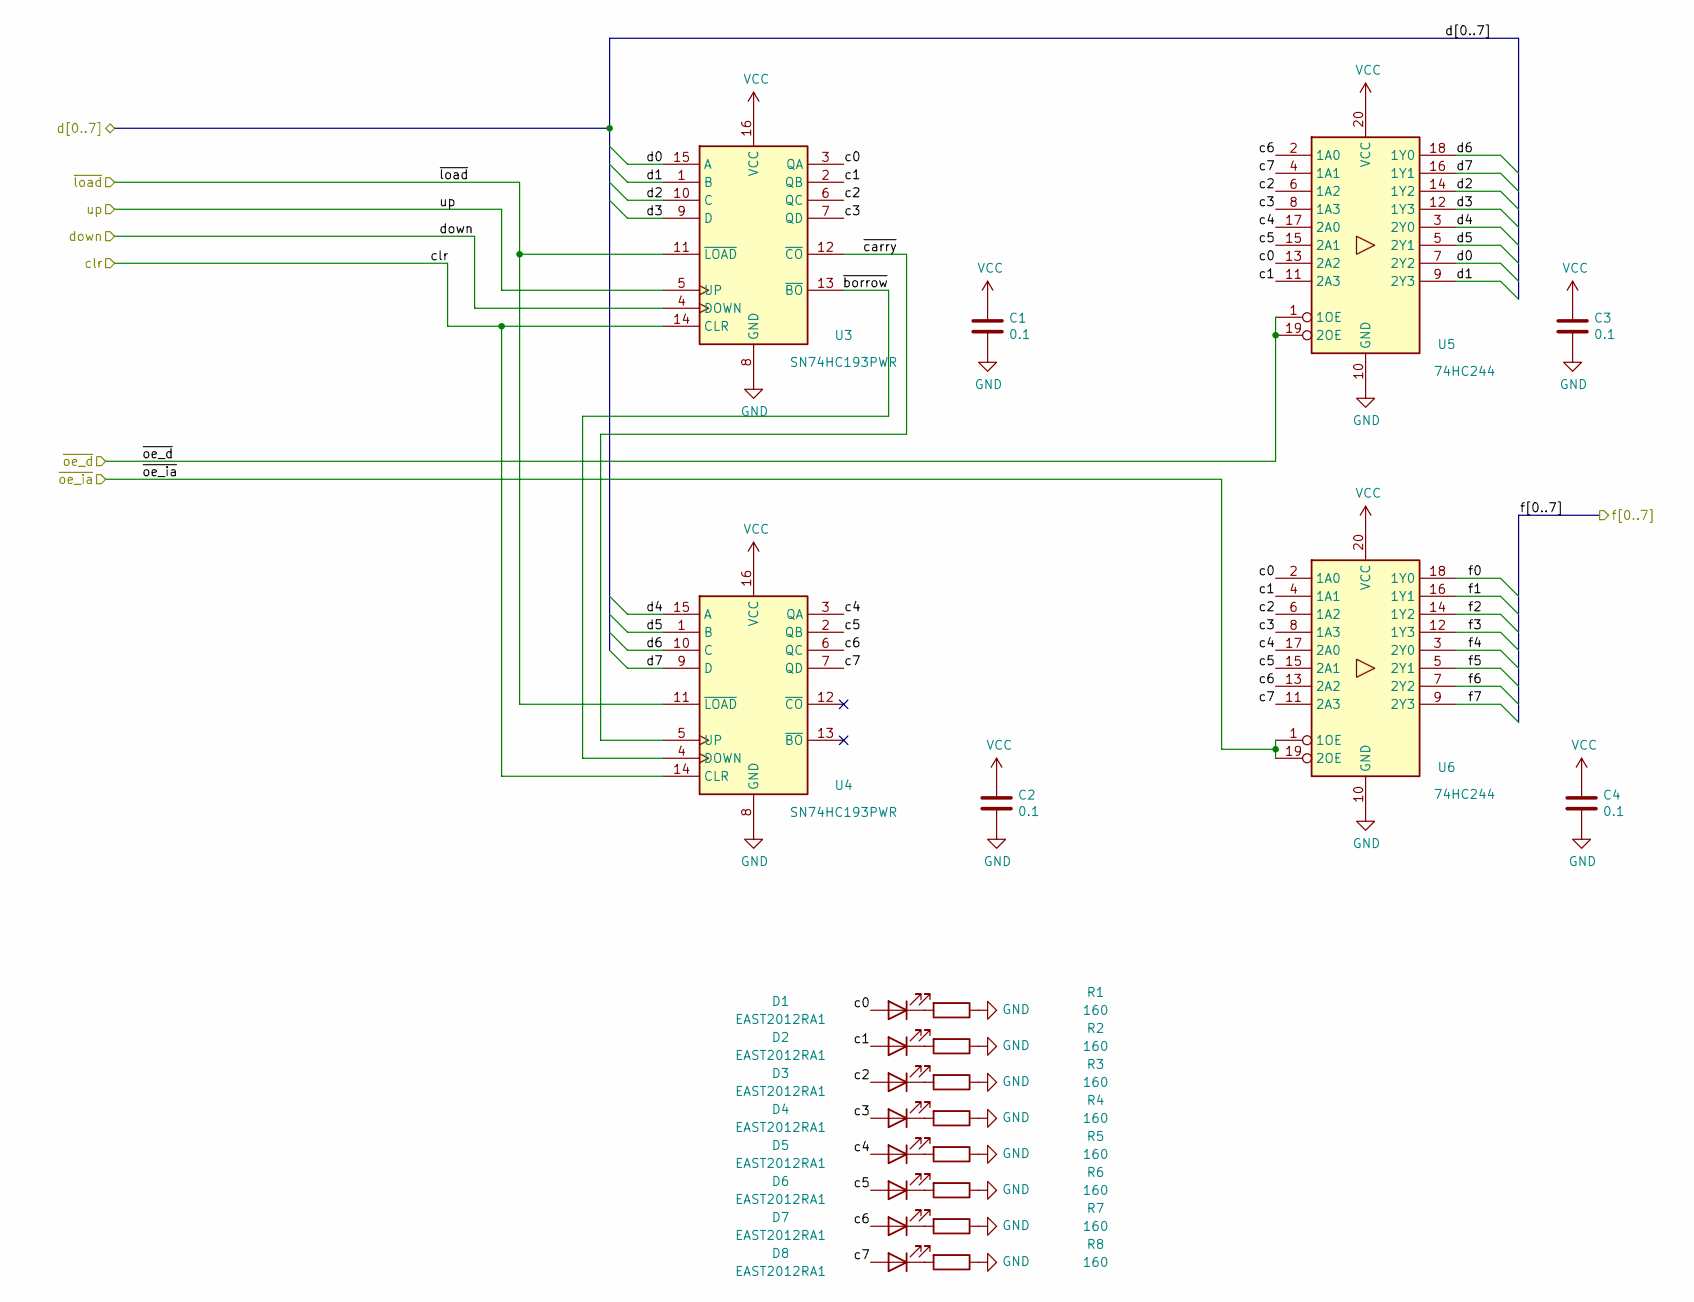
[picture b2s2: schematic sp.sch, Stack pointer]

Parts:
C1, C2, C3, C4: 0.1; C_0805_2012Metric
D1, D2, D3, D4, D5, D6, D7, D8: EAST2012RA1‎; LED_0805_2012Metric
R1, R2, R3, R4, R5, R6, R7, R8: 160; R_0805_2012Metric
U3, U4: SN74HC193PWR; TSSOP-16_4.4x5mm_P0.65mm
U5, U6: 74HC244; TSSOP-20_4.4x6.5mm_P0.65mm

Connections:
/Stack Pointer 0/c0: D1.2 (A), U3.3 (QA), U5.13 (2A2), U6.2 (1A0)
/Stack Pointer 0/c1: D2.2 (A), U3.2 (QB), U5.11 (2A3), U6.4 (1A1)
/Stack Pointer 0/c2: D3.2 (A), U3.6 (QC), U5.6 (1A2), U6.6 (1A2)
/Stack Pointer 0/c3: D4.2 (A), U3.7 (QD), U5.8 (1A3), U6.8 (1A3)
/Stack Pointer 0/c4: D5.2 (A), U4.3 (QA), U5.17 (2A0), U6.17 (2A0)
/Stack Pointer 0/c5: D6.2 (A), U4.2 (QB), U5.15 (2A1), U6.15 (2A1)
/Stack Pointer 0/c6: D7.2 (A), U4.6 (QC), U5.2 (1A0), U6.13 (2A2)
/Stack Pointer 0/c7: D8.2 (A), U4.7 (QD), U5.4 (1A1), U6.11 (2A3)
/Stack Pointer 0/~borrow: U3.13 (~BO), U4.4 (DOWN)
/Stack Pointer 0/~carry: U3.12 (~CO), U4.5 (UP)
/a11: U6.1 (1OE), U6.19 (2OE); also elsewhere on the board
/d0: U3.15 (A), U5.7 (2Y2); also elsewhere on the board
/d1: U3.1 (B), U5.9 (2Y3); also elsewhere on the board
/d2: U3.10 (C), U5.14 (1Y2); also elsewhere on the board
/d3: U3.9 (D), U5.12 (1Y3); also elsewhere on the board
/d4: U4.15 (A), U5.3 (2Y0); also elsewhere on the board
/d5: U4.1 (B), U5.5 (2Y1); also elsewhere on the board
/d6: U4.10 (C), U5.18 (1Y0); also elsewhere on the board
/d7: U4.9 (D), U5.16 (1Y1); also elsewhere on the board
/down_0: U3.4 (DOWN); also elsewhere on the board
/f0: U6.18 (1Y0); also elsewhere on the board
/f1: U6.16 (1Y1); also elsewhere on the board
/f2: U6.14 (1Y2); also elsewhere on the board
/f3: U6.12 (1Y3); also elsewhere on the board
/f4: U6.3 (2Y0); also elsewhere on the board
/f5: U6.5 (2Y1); also elsewhere on the board
/f6: U6.7 (2Y2); also elsewhere on the board
/f7: U6.9 (2Y3); also elsewhere on the board
/rst: U3.14 (CLR), U4.14 (CLR); also elsewhere on the board
/up_0: U3.5 (UP); also elsewhere on the board
/~load_0: U3.11 (~LOAD), U4.11 (~LOAD); also elsewhere on the board
/~oe_d_0: U5.1 (1OE), U5.19 (2OE); also elsewhere on the board
GND: C1.2, C2.2, C3.2, C4.2, R1.1, R2.1, R3.1, R4.1, R5.1, R6.1, R7.1, R8.1, U3.8 (GND), U4.8 (GND), U5.10 (GND), U6.10 (GND); also elsewhere on the board
unnamed: D1.1 (K), R1.2
unnamed: D2.1 (K), R2.2
unnamed: D3.1 (K), R3.2
unnamed: D4.1 (K), R4.2
unnamed: D5.1 (K), R5.2
unnamed: D6.1 (K), R6.2
unnamed: D7.1 (K), R7.2
unnamed: D8.1 (K), R8.2
VCC: C1.1, C2.1, C3.1, C4.1, U3.16 (VCC), U4.16 (VCC), U5.20 (VCC), U6.20 (VCC); also elsewhere on the board

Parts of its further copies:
C5, C6, C7, C8: 0.1; C_0805_2012Metric
D9, D10, D11, D12, D13, D14, D15, D16: EAST2012RA1‎; LED_0805_2012Metric
R9, R10, R11, R12, R13, R14, R15, R16: 160; R_0805_2012Metric
U7, U8: SN74HC193PWR; TSSOP-16_4.4x5mm_P0.65mm
U9, U10: 74HC244; TSSOP-20_4.4x6.5mm_P0.65mm

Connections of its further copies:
/Stack Pointer 1/c0: D9.2 (A), U7.3 (QA), U9.13 (2A2), U10.2 (1A0)
/Stack Pointer 1/c1: D10.2 (A), U7.2 (QB), U9.11 (2A3), U10.4 (1A1)
/Stack Pointer 1/c2: D11.2 (A), U7.6 (QC), U9.6 (1A2), U10.6 (1A2)
/Stack Pointer 1/c3: D12.2 (A), U7.7 (QD), U9.8 (1A3), U10.8 (1A3)
/Stack Pointer 1/c4: D13.2 (A), U8.3 (QA), U9.17 (2A0), U10.17 (2A0)
/Stack Pointer 1/c5: D14.2 (A), U8.2 (QB), U9.15 (2A1), U10.15 (2A1)
/Stack Pointer 1/c6: D15.2 (A), U8.6 (QC), U9.2 (1A0), U10.13 (2A2)
/Stack Pointer 1/c7: D16.2 (A), U8.7 (QD), U9.4 (1A1), U10.11 (2A3)
/Stack Pointer 1/~borrow: U7.13 (~BO), U8.4 (DOWN)
/Stack Pointer 1/~carry: U7.12 (~CO), U8.5 (UP)
/d0: U7.15 (A), U9.7 (2Y2); also elsewhere on the board
/d1: U7.1 (B), U9.9 (2Y3); also elsewhere on the board
/d2: U7.10 (C), U9.14 (1Y2); also elsewhere on the board
/d3: U7.9 (D), U9.12 (1Y3); also elsewhere on the board
/d4: U8.15 (A), U9.3 (2Y0); also elsewhere on the board
/d5: U8.1 (B), U9.5 (2Y1); also elsewhere on the board
/d6: U8.10 (C), U9.18 (1Y0); also elsewhere on the board
/d7: U8.9 (D), U9.16 (1Y1); also elsewhere on the board
/down_1: U7.4 (DOWN); also elsewhere on the board
/f0: U10.18 (1Y0); also elsewhere on the board
/f1: U10.16 (1Y1); also elsewhere on the board
/f2: U10.14 (1Y2); also elsewhere on the board
/f3: U10.12 (1Y3); also elsewhere on the board
/f4: U10.3 (2Y0); also elsewhere on the board
/f5: U10.5 (2Y1); also elsewhere on the board
/f6: U10.7 (2Y2); also elsewhere on the board
/f7: U10.9 (2Y3); also elsewhere on the board
/rst: U7.14 (CLR), U8.14 (CLR); also elsewhere on the board
/up_1: U7.5 (UP); also elsewhere on the board
/~a11: U10.1 (1OE), U10.19 (2OE); also elsewhere on the board
/~load_1: U7.11 (~LOAD), U8.11 (~LOAD); also elsewhere on the board
/~oe_d_1: U9.1 (1OE), U9.19 (2OE); also elsewhere on the board
GND: C5.2, C6.2, C7.2, C8.2, R9.1, R10.1, R11.1, R12.1, R13.1, R14.1, R15.1, R16.1, U7.8 (GND), U8.8 (GND), U9.10 (GND), U10.10 (GND); also elsewhere on the board
unnamed: D9.1 (K), R9.2
unnamed: D10.1 (K), R10.2
unnamed: D11.1 (K), R11.2
unnamed: D12.1 (K), R12.2
unnamed: D13.1 (K), R13.2
unnamed: D14.1 (K), R14.2
unnamed: D15.1 (K), R15.2
unnamed: D16.1 (K), R16.2
VCC: C5.1, C6.1, C7.1, C8.1, U7.16 (VCC), U8.16 (VCC), U9.20 (VCC), U10.20 (VCC); also elsewhere on the board

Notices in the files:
boards/alu/adder.sch:
Licensed under the TAPR Open Hardware License (www.tapr.org/OHL)
boards/alu/alu.kicad_pcb:
Licensed under the TAPR OHL
boards/eth/eth.kicad_pcb:
Copyright 2023 Ivan Mikhailov
boards/vga/vga.kicad_pcb:
Licensed under the TAPR OHL (www.tapr.org/OHL)
